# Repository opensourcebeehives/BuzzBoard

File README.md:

# BuzzBoard v1.00
Initial release of open source resources for BuzzBoard PCBA

## Feedback, Help, and Collaboration

Maintained repositories are split and located here:

Hardware: https://github.com/opensourcebeehives/BuzzBoard_hardware

Firmware: https://github.com/opensourcebeehives/BuzzBoard_firmware

Join the discussion here: [OSBeehives Forum - BuzzBoard Discussion](https://community.osbeehives.com/t/buzzboard-open-source-development-board-discussion-thread/642)

Contact us directly here: hello@osbeehives.com

## Use

See license file.

## Change Log

### v1.0
  - Initial release

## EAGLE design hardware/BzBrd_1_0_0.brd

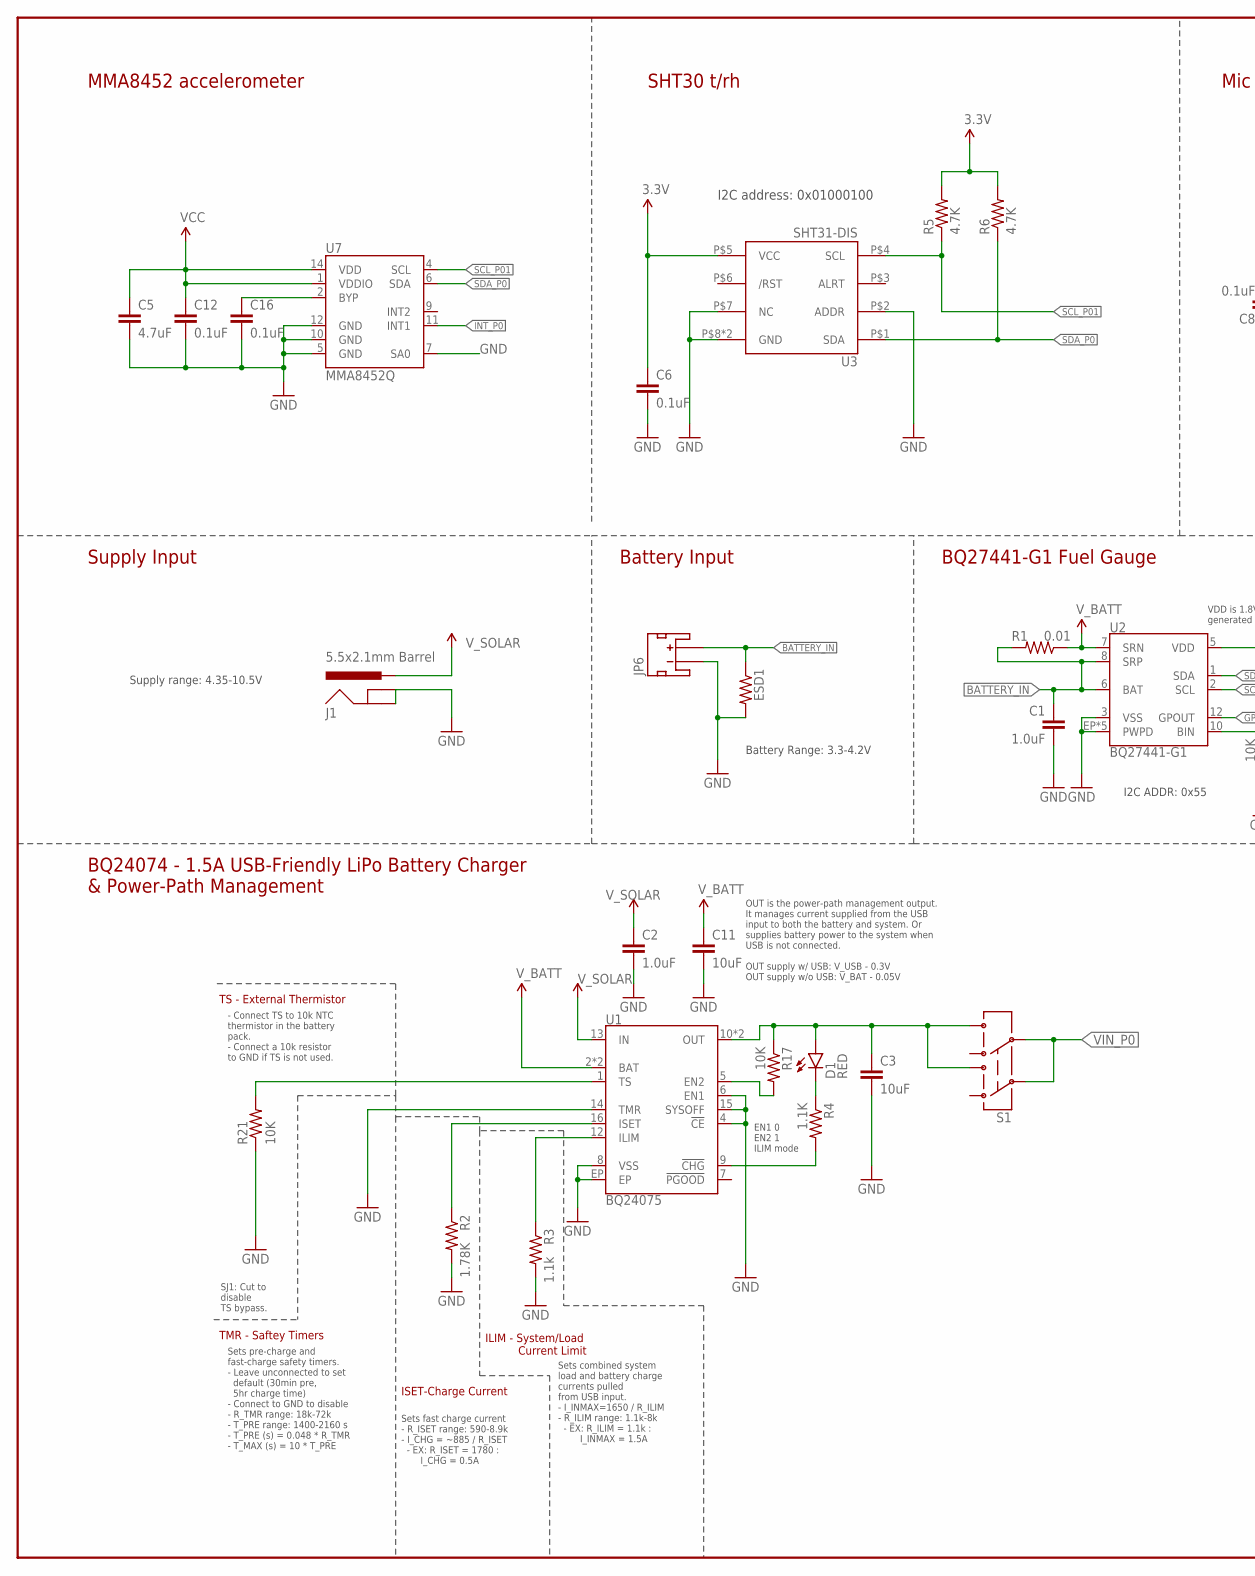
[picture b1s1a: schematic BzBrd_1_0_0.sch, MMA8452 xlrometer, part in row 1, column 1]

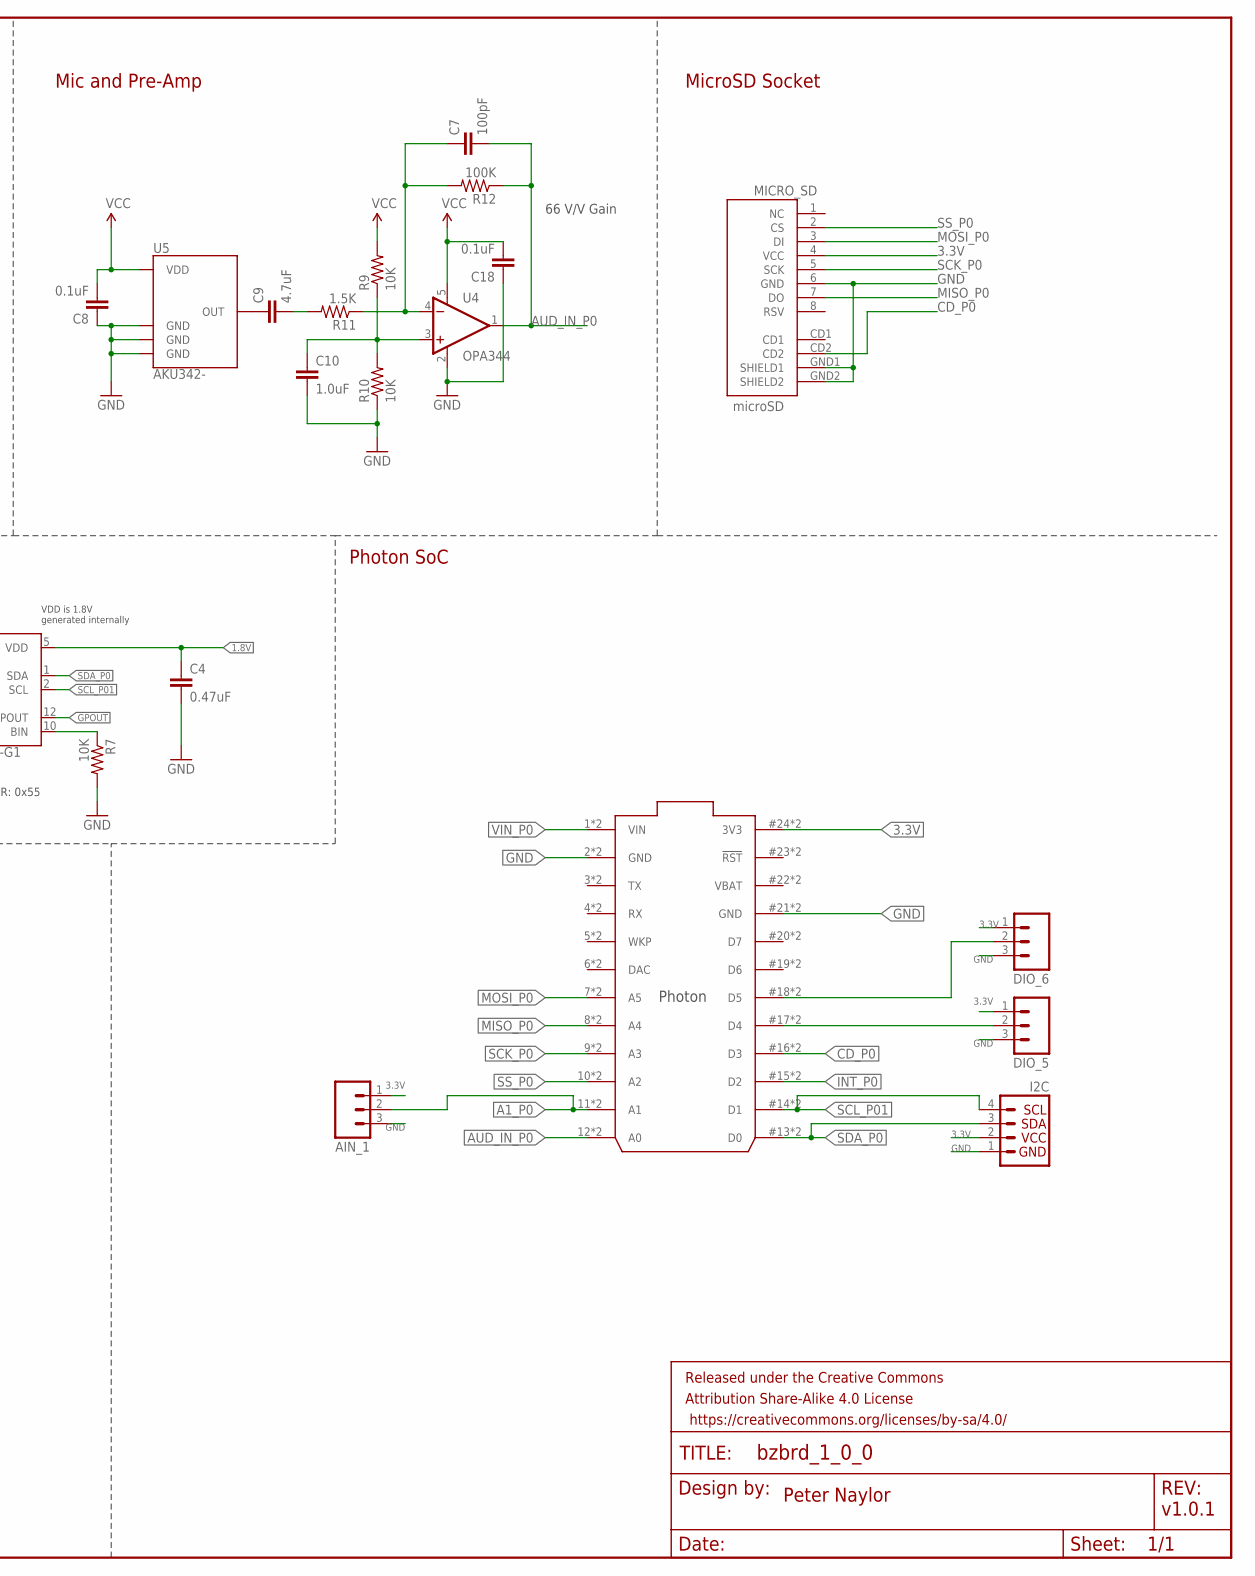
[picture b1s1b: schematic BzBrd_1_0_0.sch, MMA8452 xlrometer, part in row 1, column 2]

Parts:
AIN_1: M03LOCK_LONGPADS; 1X03_LOCK_LONGPADS
C1, C10: 1.0uF; 0603-CAP
C2: 1.0uF; 1206-CAP
C3, C11: 10uF; 0805-CAP
C4: 0.47uF; 0603-CAP
C5, C9: 4.7uF; 0603-CAP
C6, C12, C16: 0.1uF; 0603-CAP
C7: 100pF; 0402-CAP
C8, C18: 0.1uF; 0402-CAP
D1: RED; LED-0603
DIO_5, DIO_6: M03LOCK_LONGPADS; 1X03_LOCK_LONGPADS
ESD1: R-US_R0201; R0201
FRAME1: FRAME-LEDGER; CREATIVE_COMMONS
I2C: I2C_STANDARD; 1X04
J1: 5.5x2.1mm Barrel; POWER_JACK_SMD
JP6: JST_2MM_MALE; JST-2-SMD
MICRO_SD: microSD; MICRO-SD-SOCKET-PP
R1: 0.01; 1206
R2: 1.78K; 0603-RES
R3: 1.1k; 0603-RES
R4: 1.1K; 0603-RES
R5, R6: 4.7K; 0603-RES
R7, R17, R21: 10K; 0603-RES
R9, R10: 10K; 0402-RES
R11: 1.5K; 0402-RES
R12: 100K; 0402-RES
S1: SWITCH-DPDT; JCQN
U1: BQ24075; PVQFN-N16
U2: BQ27441-G1; PDSO-N12
U3: SHT31-DIS; SHT3X
U4: OPA344; SOT23-5
U5: AKU342-
U7: MMA8452Q; QFN-16_0.5MM
U$1: PHOTON_WITH_STACKABLE_HEADERS; PHOTON_STACKABLE

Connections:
1.8V: C4.1, U2.5 (VDD)
3.3V: AIN_1.1, C5.1, C6.1, C8.2, C12.1, C18.2, DIO_5.1, DIO_6.1, I2C.2, MICRO_SD.4 (VCC), R5.2, R6.2, R9.2, U3.P$5 (VCC), U4.5 (V+), U5.4 (VDD), U7.1 (VDDIO), U7.14 (VDD), U$1.24 (3V3), U$1.#24 (3V3)
!CHG!: R4.2, U1.9 (!CHG!)
A1_P0: AIN_1.2, U$1.11 (A1), U$1.@11 (A1)
AUD_IN_P0: C7.2, R12.1, U4.1 (OUT), U$1.12 (A0), U$1.@12 (A0)
BATTERY_IN: C1.1, ESD1.1, JP6.2 (+), R1.2, U2.6 (BAT), U2.8 (SRP)
CD_P0: MICRO_SD.CD2, U$1.16 (D3), U$1.#16 (D3)
GND: AIN_1.3, C1.2, C2.2, C3.2, C4.2, C5.2, C6.2, C8.1, C10.2, C11.2, C12.2, C16.2, C18.1, DIO_5.3, DIO_6.3, ESD1.2, I2C.1, J1.GND (GNDBREAK), J1.P$4 (GND), JP6.1 (-), MICRO_SD.6 (GND), MICRO_SD.GND1 (SHIELD1), MICRO_SD.GND2 (SHIELD2), R2.2, R3.2, R7.2, R10.1, R21.1, U1.4 (!CE!), U1.6 (EN1), U1.8 (VSS), U1.14 (TMR), U1.15 (SYSOFF), U1.EP, U2.3 (VSS), U2.EP (PWPD), U2.EP1 (PWPD), U2.EP2 (PWPD), U2.EP3 (PWPD), U2.EP4 (PWPD), U3.P$2 (ADDR), U3.P$7 (NC), U3.P$8 (GND), U3.PAD (GND), U4.2 (V-), U5.2 (GND), U5.3 (GND), U5.5 (GND), U7.5 (GND), U7.7 (SA0), U7.10 (GND), U7.12 (GND), U$1.2 (GND), U$1.21 (GND), U$1.#21 (GND), U$1.@2 (GND)
GPOUT: U2.12 (GPOUT)
ILIM: R3.1, U1.12 (ILIM)
INT_P0: U7.11 (INT1), U$1.15 (D2), U$1.#15 (D2)
ISET: R2.1, U1.16 (ISET)
MISO_P0: MICRO_SD.7 (DO), U$1.8 (A4), U$1.@8 (A4)
MOSI_P0: MICRO_SD.3 (DI), U$1.7 (A5), U$1.@7 (A5)
unnamed: D1.C, R4.1
unnamed: R7.1, U2.10 (BIN)
unnamed: R17.2, U1.5 (EN2)
unnamed: C16.1, U7.2 (BYP)
unnamed: C9.1, U5.1 (OUT)
unnamed: C7.1, R11.1, R12.2, U4.4 (-IN)
unnamed: C9.2, R11.2
unnamed: C10.1, R9.1, R10.2, U4.3 (+IN)
unnamed: DIO_5.2, U$1.17 (D4), U$1.#17 (D4)
unnamed: DIO_6.2, U$1.18 (D5), U$1.#18 (D5)
SCK_P0: MICRO_SD.5 (SCK), U$1.9 (A3), U$1.@9 (A3)
SCL_P01: I2C.4, R5.1, U2.2 (SCL), U3.P$4 (SCL), U7.4 (SCL), U$1.14 (D1), U$1.#14 (D1)
SDA_P0: I2C.3, R6.1, U2.1 (SDA), U3.P$1 (SDA), U7.6 (SDA), U$1.13 (D0), U$1.#13 (D0)
SS_P0: MICRO_SD.2 (CS), U$1.10 (A2), U$1.@10 (A2)
TS: R21.2, U1.1 (TS)
VBAT: U$1.22 (VBAT), U$1.#22 (VBAT)
VIN_P0: S1.P$2 (2), S1.P$5 (5), U$1.1 (VIN), U$1.@1 (VIN)
VOUT_SOL: C3.1, D1.A, R17.1, S1.P$3 (3), S1.P$6 (6), U1.10 (OUT), U1.11 (OUT)
V_BATT: C11.1, R1.1, U1.2 (BAT), U1.3 (BAT), U2.7 (SRN)
V_SOLAR: C2.1, J1.VIN0 (PWR), U1.13 (IN)

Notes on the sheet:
Sets fast charge current - R_ISET range: 590-8.9k - I_CHG = ~885 / R_ISET - EX: R_ISET = 1780 : I_CHG = 0.5A
Sets combined system load and battery charge currents pulled from USB input. - I_INMAX=1650 / R_ILIM - R_ILIM range: 1.1k-8k - EX: R_ILIM = 1.1k : I_INMAX = 1.5A
Supply Input
Battery Input
BQ24074 - 1.5A USB-Friendly LiPo Battery Charger & Power-Path Management
BQ27441-G1 Fuel Gauge
Peter Naylor
SJ1: Cut to disable TS bypass.
ILIM - System/Load Current Limit
ISET-Charge Current
TMR - Saftey Timers
Sets pre-charge and fast-charge safety timers. - Leave unconnected to set default (30min pre, 5hr charge time) - Connect to GND to disable - R_TMR range: 18k-72k - T_PRE range: 1400-2160 s - T_PRE (s) = 0.048 * R_TMR - T_MAX (s) = 10 * T_PRE
TS - External Thermistor
- Connect TS to 10k NTC thermistor in the battery pack. - Connect a 10k resistor to GND if TS is not used.
Supply range: 4.35-10.5V
VDD is 1.8V generated internally
OUT is the power-path management output. It manages current supplied from the USB input to both the battery and system. Or supplies battery power to the system when USB is not connected. OUT supply w/ USB: V_USB - 0.3V OUT supply w/o USB: V_BAT - 0.05V
I2C ADDR: 0x55
Battery Range: 3.3-4.2V
EN1 0 EN2 1 ILIM mode
I2C address: 0x01000100
66 V/V Gain
Mic and Pre-Amp
SHT30 t/rh
MMA8452 accelerometer
Photon SoC
MicroSD Socket
v1.0.1

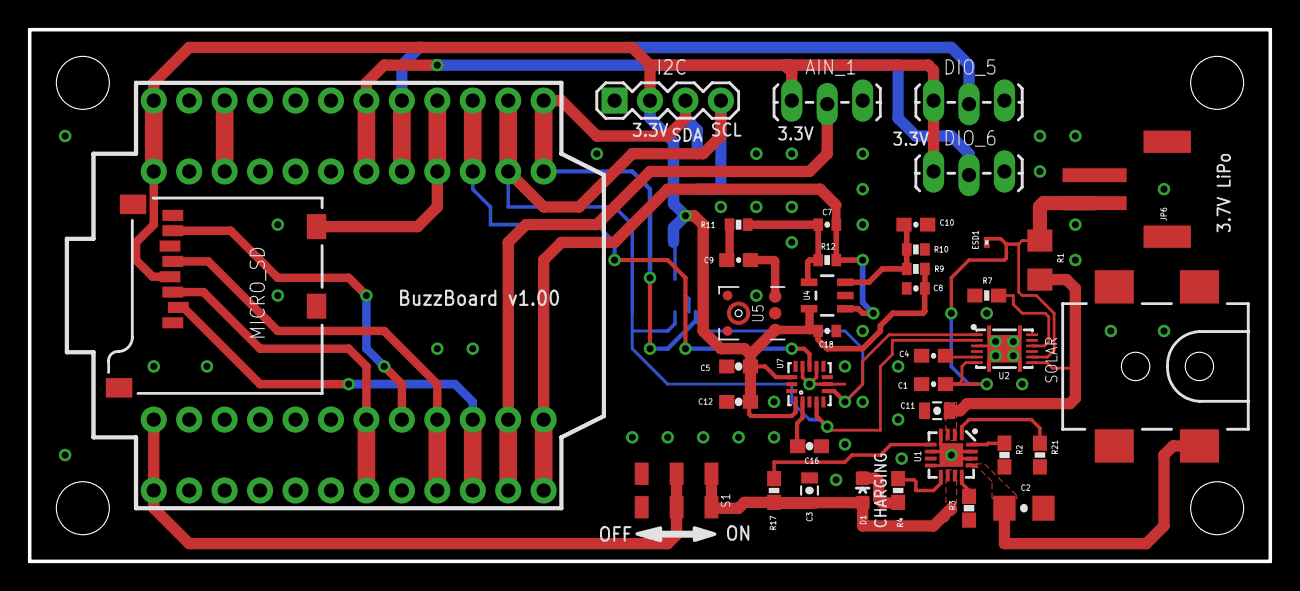
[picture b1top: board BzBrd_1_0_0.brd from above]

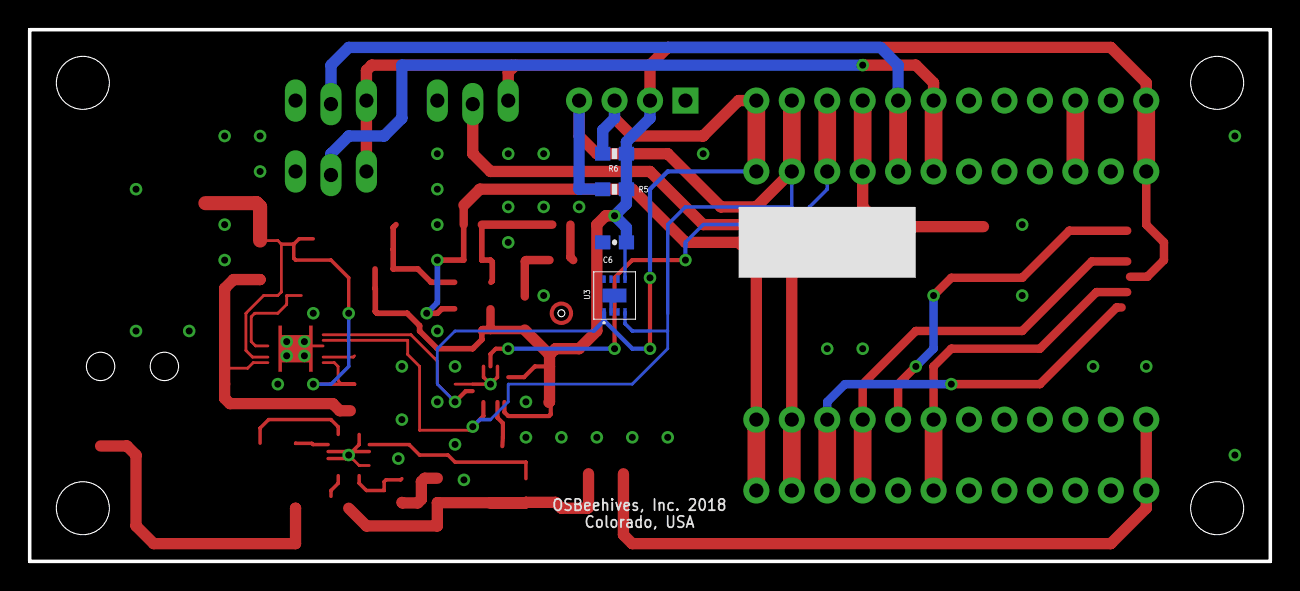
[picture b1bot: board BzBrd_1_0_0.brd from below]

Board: 2 copper layers, 88.9 x 38.1 mm, 49 parts (4 on the bottom side), 33 nets.

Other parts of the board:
U$2, U$3, U$4, U$5: STAND-OFF

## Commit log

2018-06-19 Added .gitignore
2018-06-19 Removed .DS_Store files from firmware and hardware folders
2018-06-20 one schematic sheet
2018-06-29 split repo msg
2018-06-29 split repo message
2018-06-29 moved repos

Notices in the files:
parts and their libraries:
SparkFun-Capacitors: Licensing: Creative Commons ShareAlike 4.0 International - https://creativecommons.org/licenses/by-sa/4.0
Particle-Devices: Licensing: Designed by Particle.
SparkFun-Aesthetics: Released under the Creative Commons Attribution Share-Alike 4.0 License
